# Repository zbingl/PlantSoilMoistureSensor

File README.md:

# Plant Soil Moisture Sensor

A compact soil moisture sensing system including custom PCB designs, 3D printable casing, and firmware source code.

## Hardware & Schematics

### PCB Layout & Schematic
| Schematic | PCB Design |
| :---: | :---: |
|  |  |

---

## Gallery

| Top View | Top-Side View 1 | Top-Side View 2 |
| :---: | :---: | :---: |
|  |  |  |

---

## Project Structure

```text
PlantSoilMoistureSensor/
├── case/     # 3D printable case / CAD files
├── media/    # Images and project media
├── pcb/      # KiCad PCB schematics and layout
└── src/      # Firmware source code

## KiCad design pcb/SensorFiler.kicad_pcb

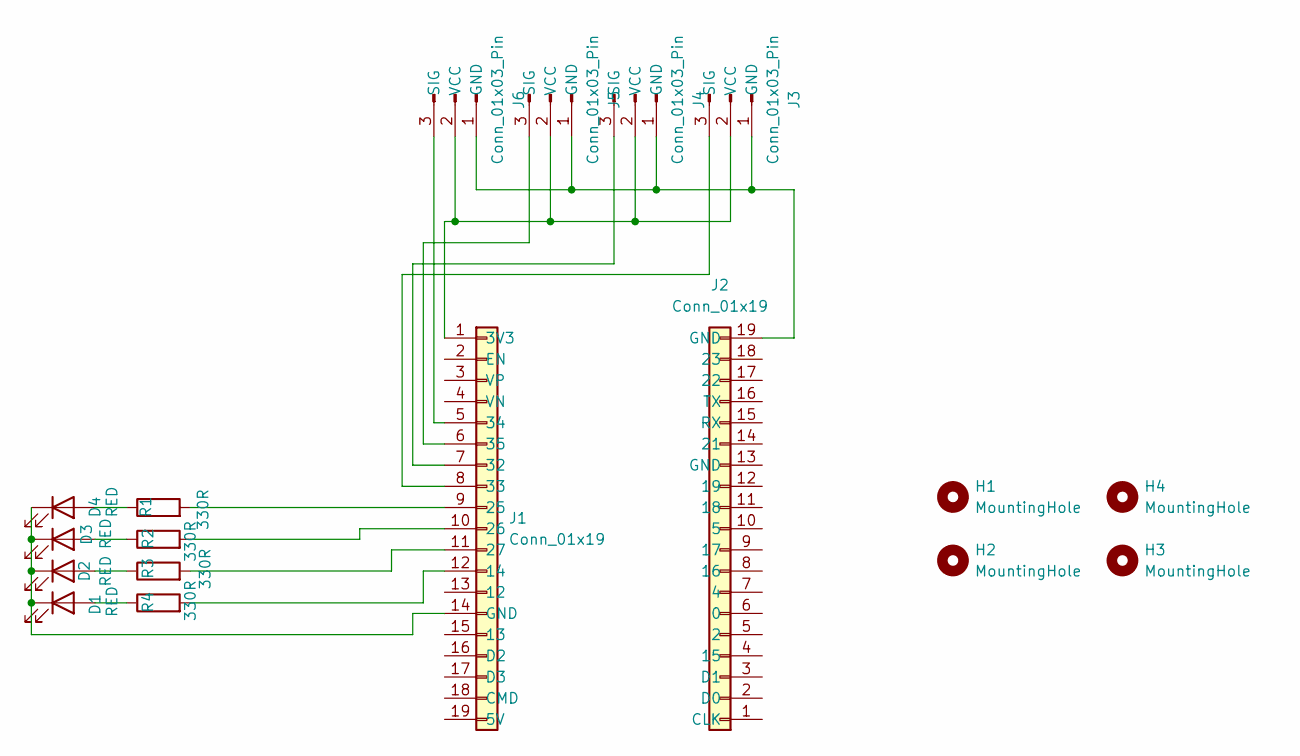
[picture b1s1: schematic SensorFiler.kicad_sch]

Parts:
D1, D2, D3, D4: RED; LED_D5.0mm
H1, H2, H3, H4: MountingHole; MountingHole_3.2mm_M3
J1, J2: Conn_01x19; PinSocket_1x19_P2.54mm_Vertical
J3, J4, J5, J6: Conn_01x03_Pin; PinHeader_1x03_P2.54mm_Vertical
R1, R2, R3, R4: 330R; R_Axial_DIN0207_L6.3mm_D2.5mm_P10.16mm_Horizontal

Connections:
unnamed: D1.2 (A), R4.1
unnamed: D1.1 (K), D2.1 (K), D3.1 (K), D4.1 (K), J1.14 (GND)
unnamed: D2.2 (A), R3.1
unnamed: D3.2 (A), R2.1
unnamed: D4.2 (A), R1.1
unnamed: J1.1 (3V3), J3.2 (VCC), J4.2 (VCC), J5.2 (VCC), J6.2 (VCC)
unnamed: J1.12 (14), R4.2
unnamed: J1.9 (25), R1.2
unnamed: J1.10 (26), R2.2
unnamed: J1.11 (27), R3.2
unnamed: J1.7 (32), J4.3 (SIG)
unnamed: J1.8 (33), J3.3 (SIG)
unnamed: J1.5 (34), J6.3 (SIG)
unnamed: J1.6 (35), J5.3 (SIG)
unnamed: J2.19 (GND_19), J3.1 (GND), J4.1 (GND), J5.1 (GND), J6.1 (GND)

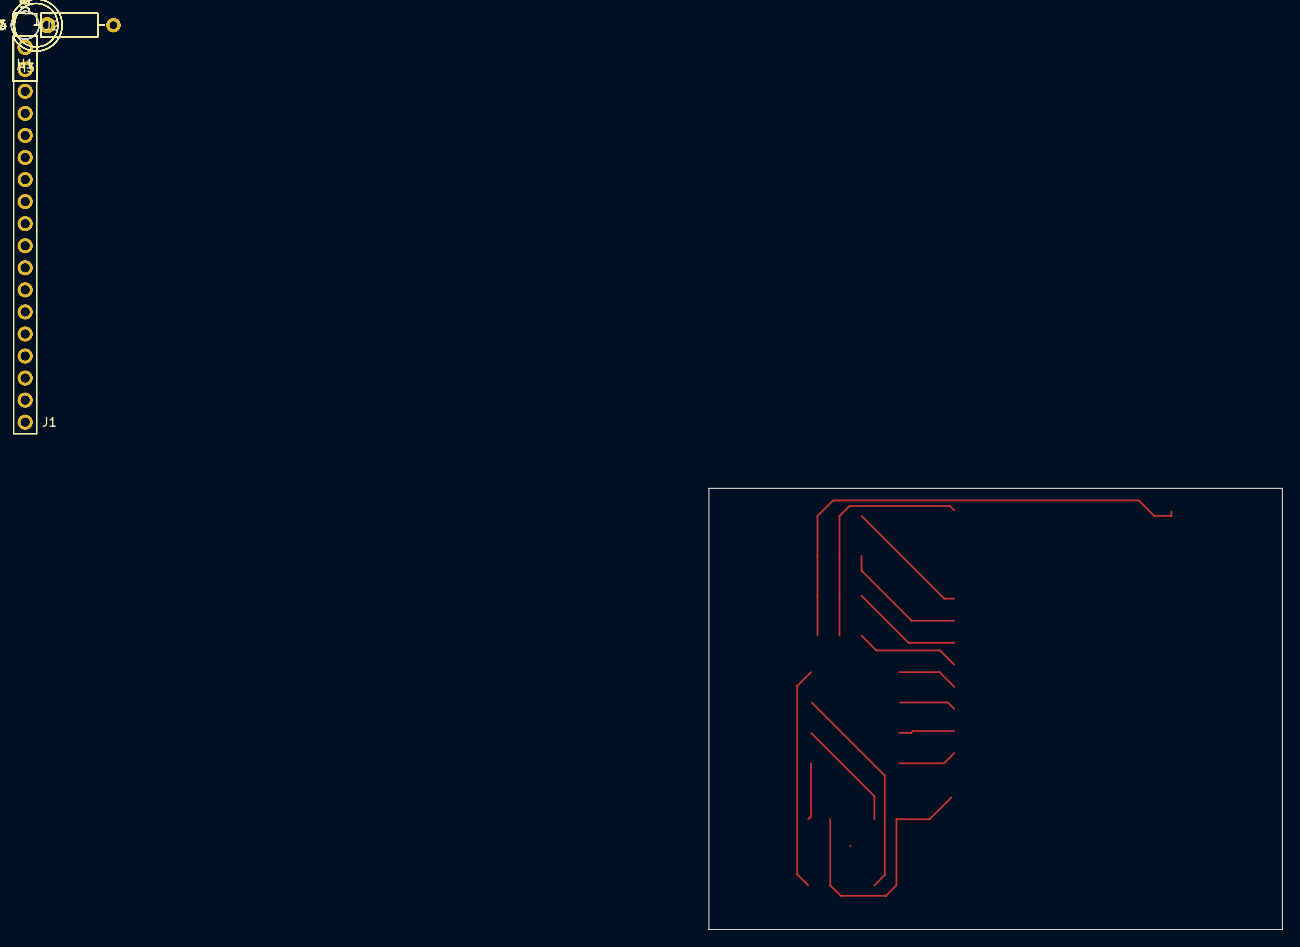
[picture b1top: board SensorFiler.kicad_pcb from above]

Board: 2 copper layers, 66.0 x 50.8 mm, 18 parts (0 on the bottom side), 15 nets.
